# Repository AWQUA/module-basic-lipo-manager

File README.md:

# module-basic-lipo-manager
A simple, breadboard-ready lipo manager

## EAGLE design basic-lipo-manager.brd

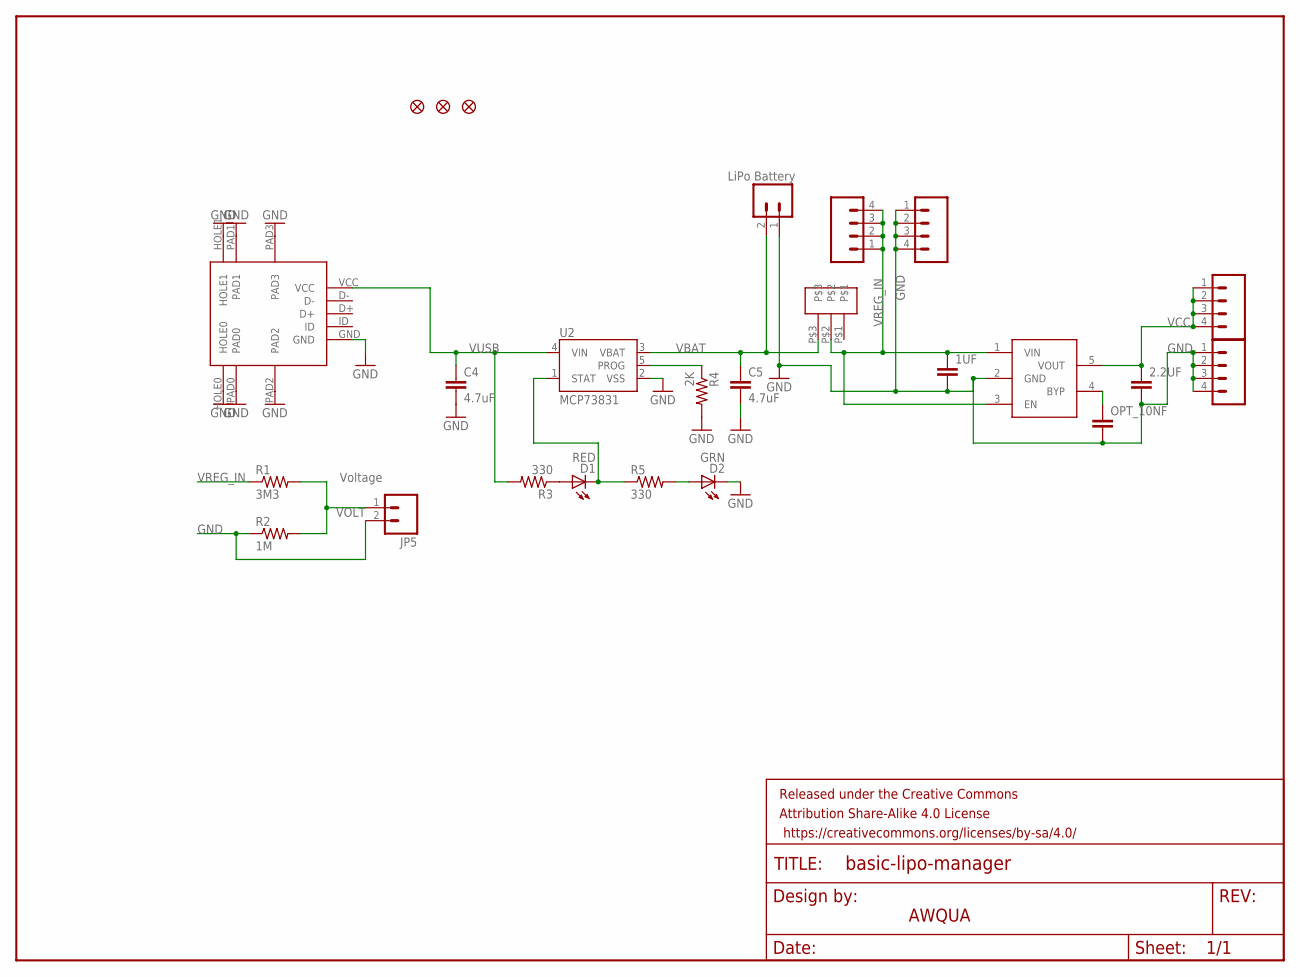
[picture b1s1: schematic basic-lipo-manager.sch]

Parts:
1UF, 2.2UF: CAP0603-CAP; 0603-CAP
C4, C5: 4.7uF; 0402-CAP
D1: RED; LED-0603
D2: GRN; LED-0603
FID1, FID2, FID3: FIDUCIAL1X2; FIDUCIAL-1X2
FRAME1: FRAME-LETTER; CREATIVE_COMMONS
JP1, JP2, JP3, JP4: M04PTH; 1X04
JP5: M02PTH; 1X02
JP7: LiPo Battery; JST-2-SMD
OPT_10NF: CAP0603-CAP; 0603-CAP
R1: 3M3; 0603-RES
R2: 1M; 0603-RES
R3, R5: 330; 0402-RES
R4: 2K; 0402-RES
U2: MCP73831; SOT23-5
U$3: USBMICRO-10118193-0001LF
U$6: LP2985
U$7: OS102-SPDT-SWITCH

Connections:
BYPASS: OPT_10NF.1, U$6.4 (BYP)
GND: 1UF.2, 2.2UF.2, C4.2, C5.2, D2.C, JP2.1, JP2.2, JP2.3, JP2.4, JP4.1, JP4.2, JP4.3, JP4.4, JP5.2, JP7.1, OPT_10NF.2, R2.1, R4.2, U2.2 (VSS), U$3.GND, U$3.HOLE0, U$3.HOLE1, U$3.PAD0, U$3.PAD1, U$3.PAD2, U$3.PAD3, U$6.2 (GND)
unnamed: D1.A, R3.1
unnamed: D2.A, R5.2
PROG: R4.1, U2.5 (PROG)
STAT: D1.C, R5.1, U2.1 (STAT)
VBAT: C5.1, JP7.2, U2.3 (VBAT), U$7.P$3
VCC: 2.2UF.1, JP3.1, JP3.2, JP3.3, JP3.4, U$6.5 (VOUT)
VOLT: JP5.1, R1.2, R2.2
VREG_IN: 1UF.1, JP1.1, JP1.2, JP1.3, JP1.4, R1.1, U$6.1 (VIN), U$6.3 (EN), U$7.P$2
VUSB: C4.1, R3.2, U2.4 (VIN), U$3.VCC

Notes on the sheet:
AWQUA
Voltage

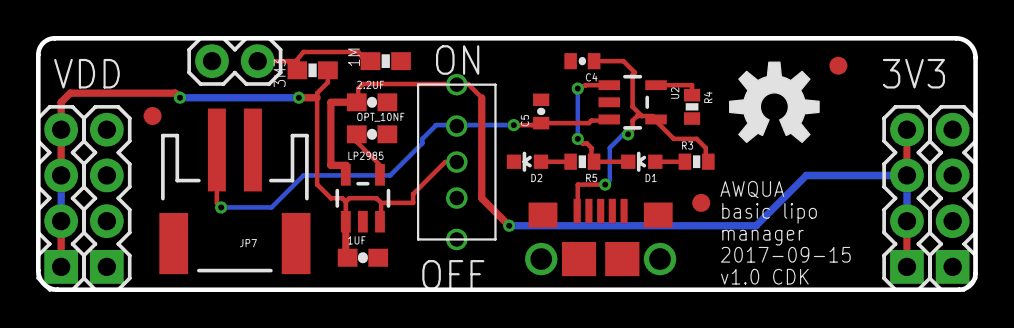
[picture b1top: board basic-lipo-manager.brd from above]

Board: 2 copper layers, 52.1 x 14.0 mm, 27 parts (0 on the bottom side), 11 nets.

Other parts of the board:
U$4: OSHW-LOGO-M

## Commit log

2017-09-15 initial pusjh
2017-09-19 label edits, fiducials added

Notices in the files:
parts and their libraries:
SparkFun-Resistors: Licensing: CC v3.0 Share-Alike You are welcome to use this library for commercial purposes.
SparkFun-Aesthetics: Released under the Creative Commons Attribution Share-Alike 4.0 License
SparkFun-Aesthetics: https://creativecommons.org/licenses/by-sa/4.0
